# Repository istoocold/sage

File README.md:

# SAGE
 Introduction
--------------------------------------------
Name based on metaphor of a monk like Sage here means this pocket handheld device can do very things. I prominently design it for as belt jewellery, AI desk assistant, game handheld(after little adjustment)

## Build

It have BOM, Custom PCB, 3D printed Enclosure, buttons and suport.
Download All files(.stp) from Enclosure printable folder and print 'em
 > It uses M2 screw everywhere
 
 > In assembly u may see the MCU as colliding with PCB dw! it just cz I can't remove the header pins. :lollll:

 ### Instructions
 > First of all we will solder wire on every solder pad and then make a bunch of them together.
 > now comes the MCU U hve to castellated solder it on top of the board or can use very low height header pins. we can have access to wire below the MCU and then connect them their respective components. 
 > Then Place components using supports provided using screws and tape/glue as required.
 > Use a double sided tape to mount battery here
 > 

## Code
This requires basic firmware code u can compile and flash it in MCU using Platform.io (a extension in VS code) or using Thonny (IDE)

## How to use it:
For Navigation use button , U can directly flash a bit game in with button. The software for that is still in developments.loll

# AI- decl.
I use like very little < 10% AI for code. 

# Outro
Made for Hackclub <3 by Iksha
Feel free to contribute :heart:

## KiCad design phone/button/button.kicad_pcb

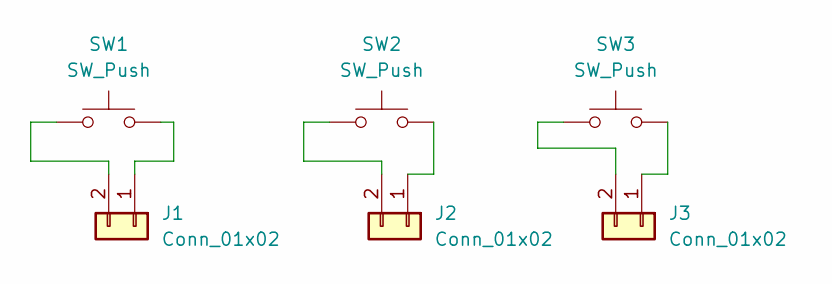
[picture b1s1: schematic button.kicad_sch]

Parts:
J1, J2, J3: Conn_01x02; SolderWirePad_1x02_SMD_5x5mm
SW1, SW2, SW3: SW_Push; SW_PUSH_6mm

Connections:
unnamed: J1.1, SW1.2
unnamed: J1.2, SW1.1
unnamed: J2.2, SW2.1
unnamed: J2.1, SW2.2
unnamed: J3.2, SW3.1
unnamed: J3.1, SW3.2

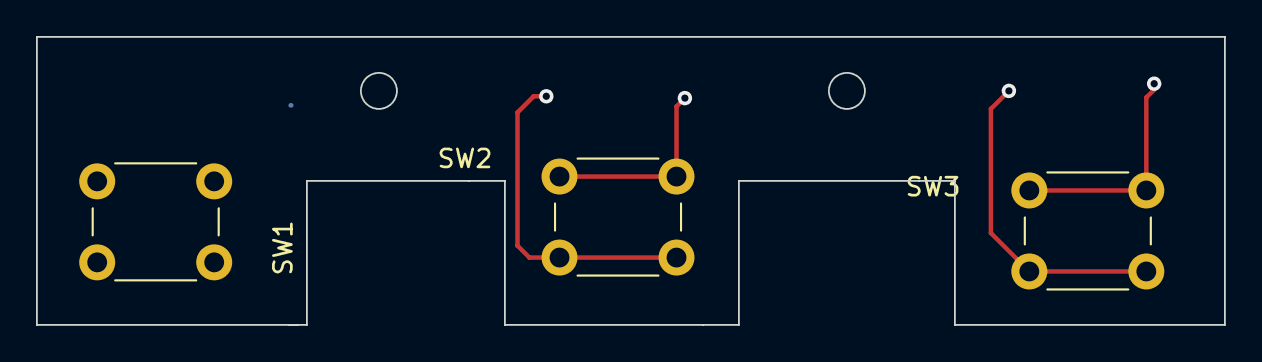
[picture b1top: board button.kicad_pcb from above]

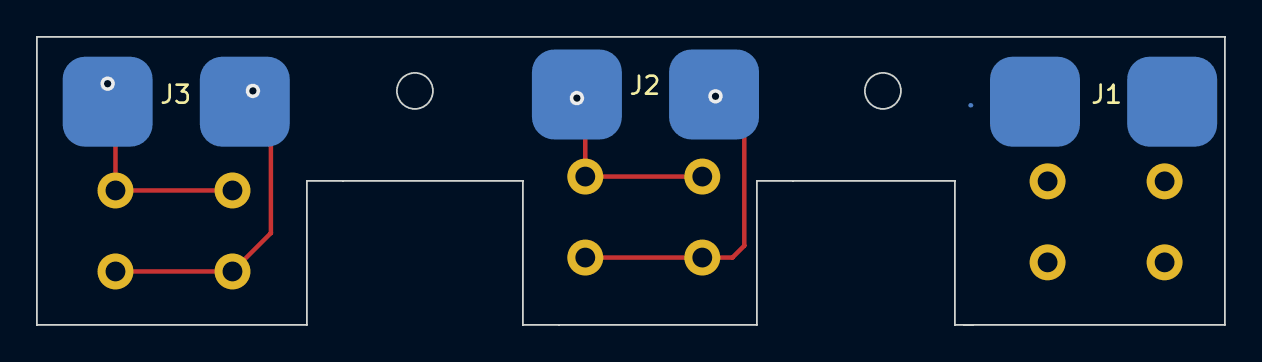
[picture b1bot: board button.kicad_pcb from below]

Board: 2 copper layers, 66.0 x 16.0 mm, 6 parts (3 on the bottom side), 6 nets.

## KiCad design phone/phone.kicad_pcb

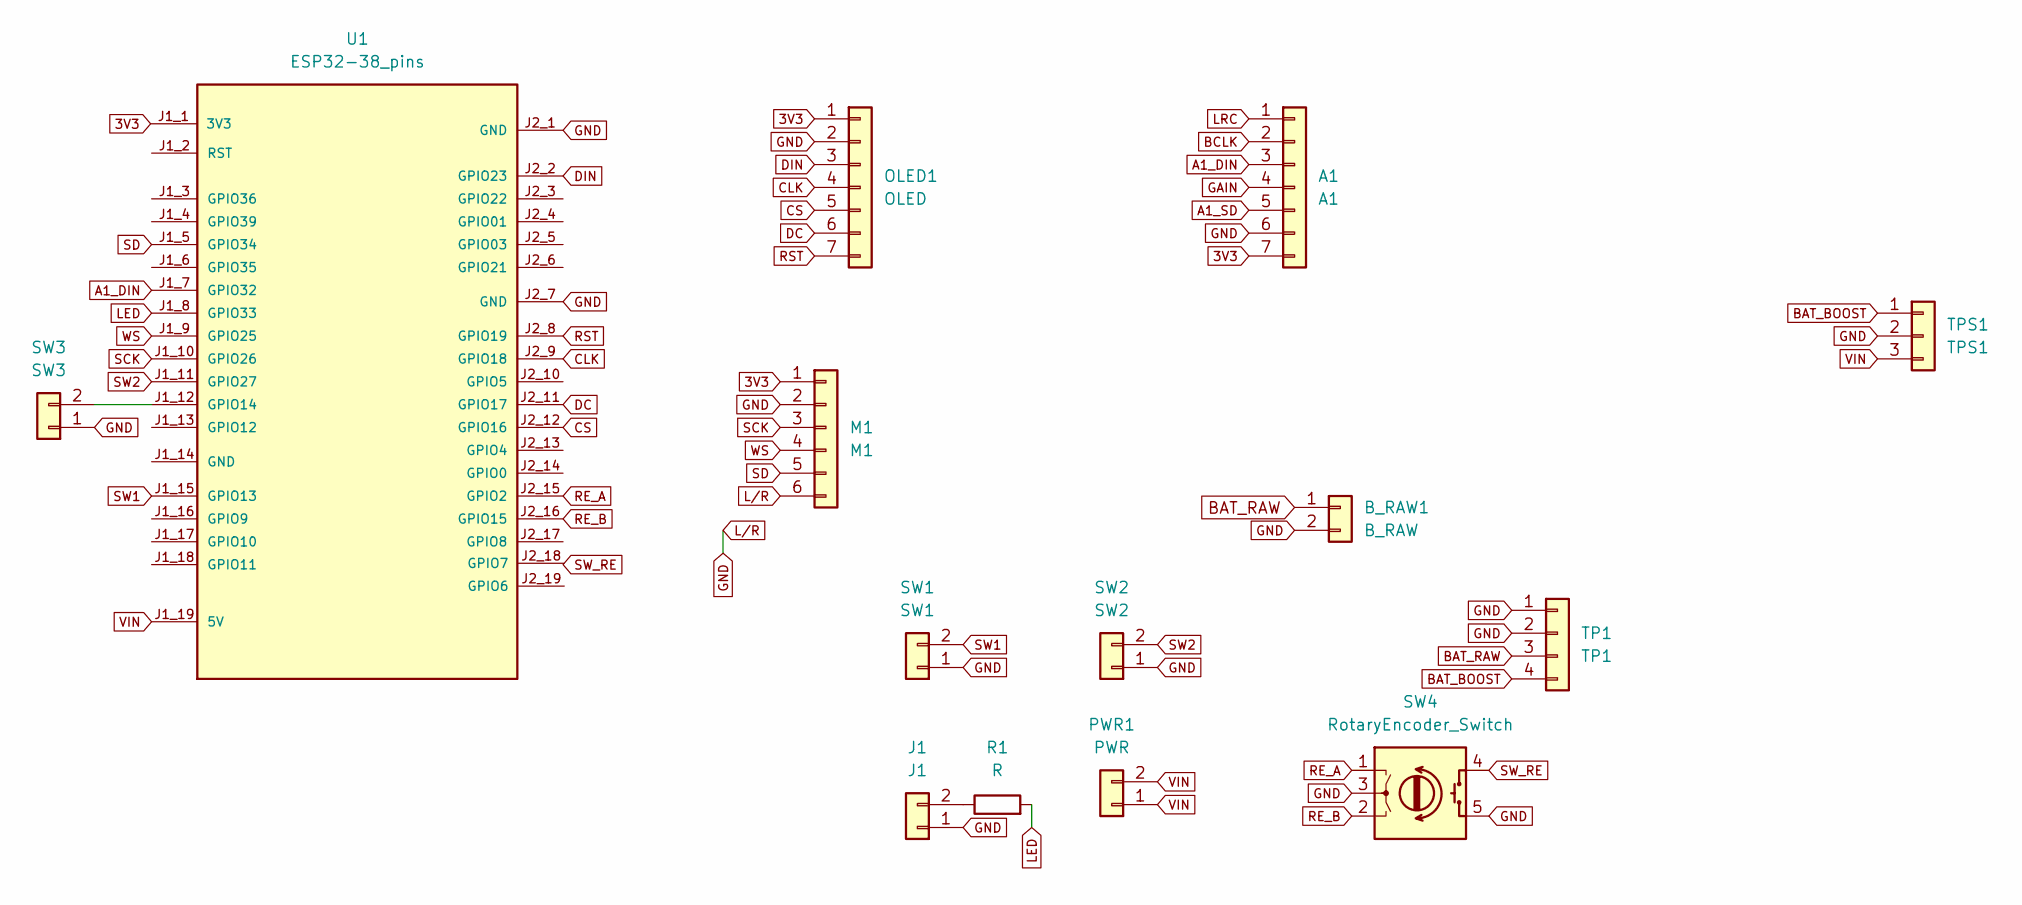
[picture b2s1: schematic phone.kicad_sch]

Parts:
A1: A1; SolderWirePad_1x07_SMD_2x6mm
B_RAW1: B_RAW; SolderWirePad_1x02_SMD_2x6mm
J1: J1; SolderWirePad_1x02_SMD_2x6mm
M1: M1; SolderWirePad_1x06_SMD_2x6mm
OLED1: OLED; SolderWirePad_1x07_SMD_2x6mm
PWR1: PWR; SolderWirePad_1x02_SMD_2x6mm
R1: R; R_Axial_DIN0207_L6.3mm_D2.5mm_P7.62mm_Horizontal
SW1: SW1; SolderWirePad_1x02_SMD_2x6mm
SW2: SW2; SolderWirePad_1x02_SMD_2x6mm
SW3: SW3; SolderWirePad_1x02_SMD_2x6mm
SW4: RotaryEncoder_Switch; SolderWirePad_1x05_SMD_2x6mm
TP1: TP1; SolderWirePad_1x04_SMD_2x6mm
TPS1: TPS1; SolderWirePad_1x03_SMD_2x6mm
U1: ESP32-38_pins; MODULE_ESP32_NODEMCU; PARTREV 1.1; DigiKey_Part_Number 1965-ESP32-S3-DEVKITC-1U-N8R8-ND

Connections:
3V3: A1.7, M1.1, OLED1.1, U1.J1_1 (3V3)
A1_DIN: A1.3, U1.J1_7 (GPIO32)
A1_SD: A1.5
BAT_BOOST: TP1.4, TPS1.1
BAT_RAW: B_RAW1.1, TP1.3
BCLK: A1.2
CLK: OLED1.4, U1.J2_9 (GPIO18)
CS: OLED1.5, U1.J2_12 (GPIO16)
DC: OLED1.6, U1.J2_11 (GPIO17)
DIN: OLED1.3, U1.J2_2 (GPIO23)
GAIN: A1.4
GND: A1.6, B_RAW1.2, J1.1, M1.2, M1.6, OLED1.2, SW1.1, SW2.1, SW3.1, SW4.3 (C), SW4.5 (S2), TP1.1, TP1.2, TPS1.2, U1.J2_1 (GND), U1.J2_7 (GND)
LED: R1.2, U1.J1_8 (GPIO33)
LRC: A1.1
unnamed: J1.2, R1.1
unnamed: SW3.2, U1.J1_12 (GPIO14)
RE_A: SW4.1 (A), U1.J2_15 (GPIO2)
RE_B: SW4.2 (B), U1.J2_16 (GPIO15)
RST: OLED1.7, U1.J2_8 (GPIO19)
SCK: M1.3, U1.J1_10 (GPIO26)
SD: M1.5, U1.J1_5 (GPIO34)
SW1: SW1.2, U1.J1_15 (GPIO13)
SW2: SW2.2, U1.J1_11 (GPIO27)
SW_RE: SW4.4 (S1)
VIN: PWR1.1, PWR1.2, TPS1.3, U1.J1_19 (5V)
WS: M1.4, U1.J1_9 (GPIO25)

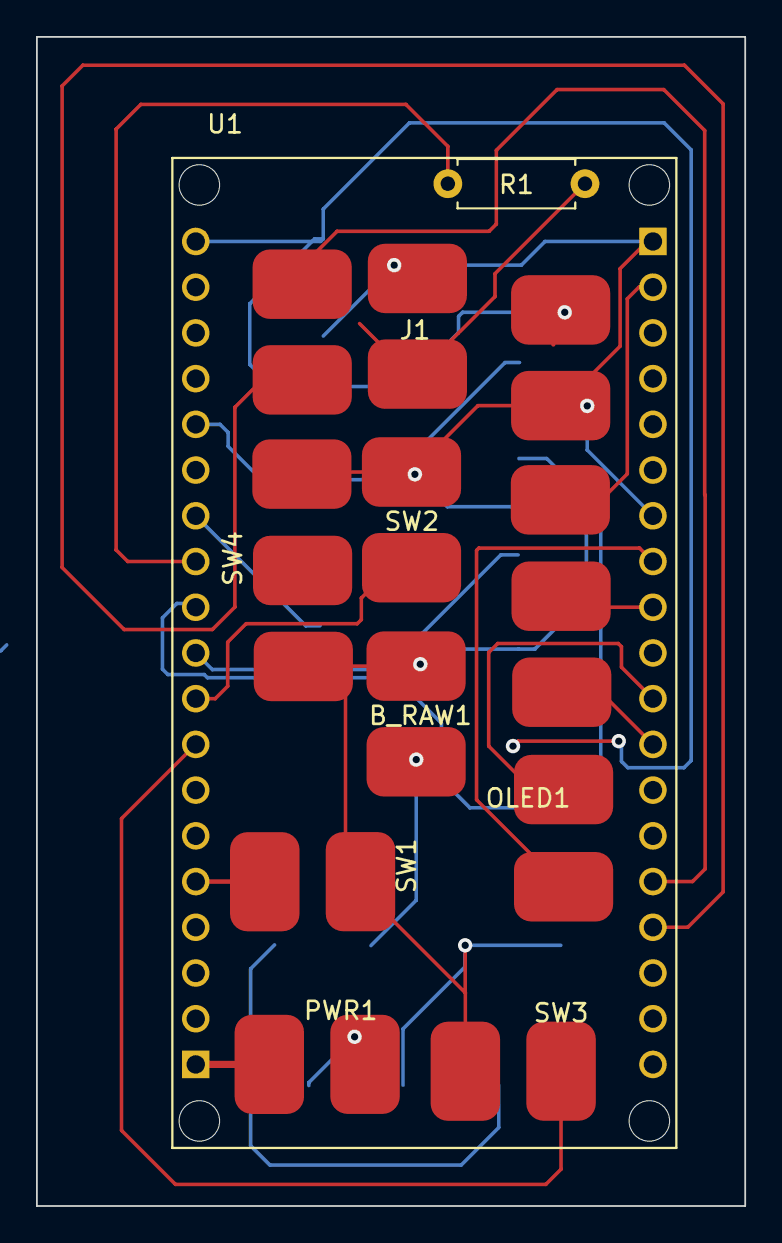
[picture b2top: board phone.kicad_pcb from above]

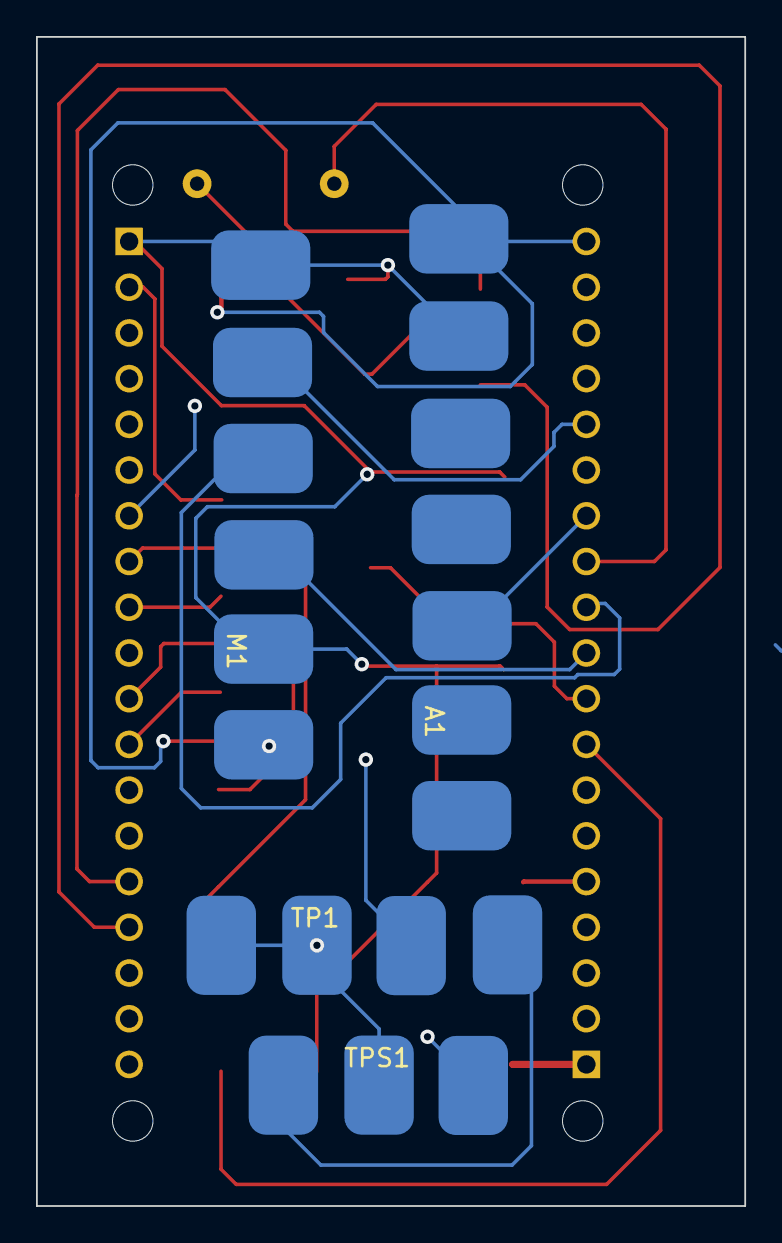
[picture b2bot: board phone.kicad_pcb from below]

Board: 2 copper layers, 39.3 x 65.0 mm, 14 parts (4 on the bottom side), 21 nets.
